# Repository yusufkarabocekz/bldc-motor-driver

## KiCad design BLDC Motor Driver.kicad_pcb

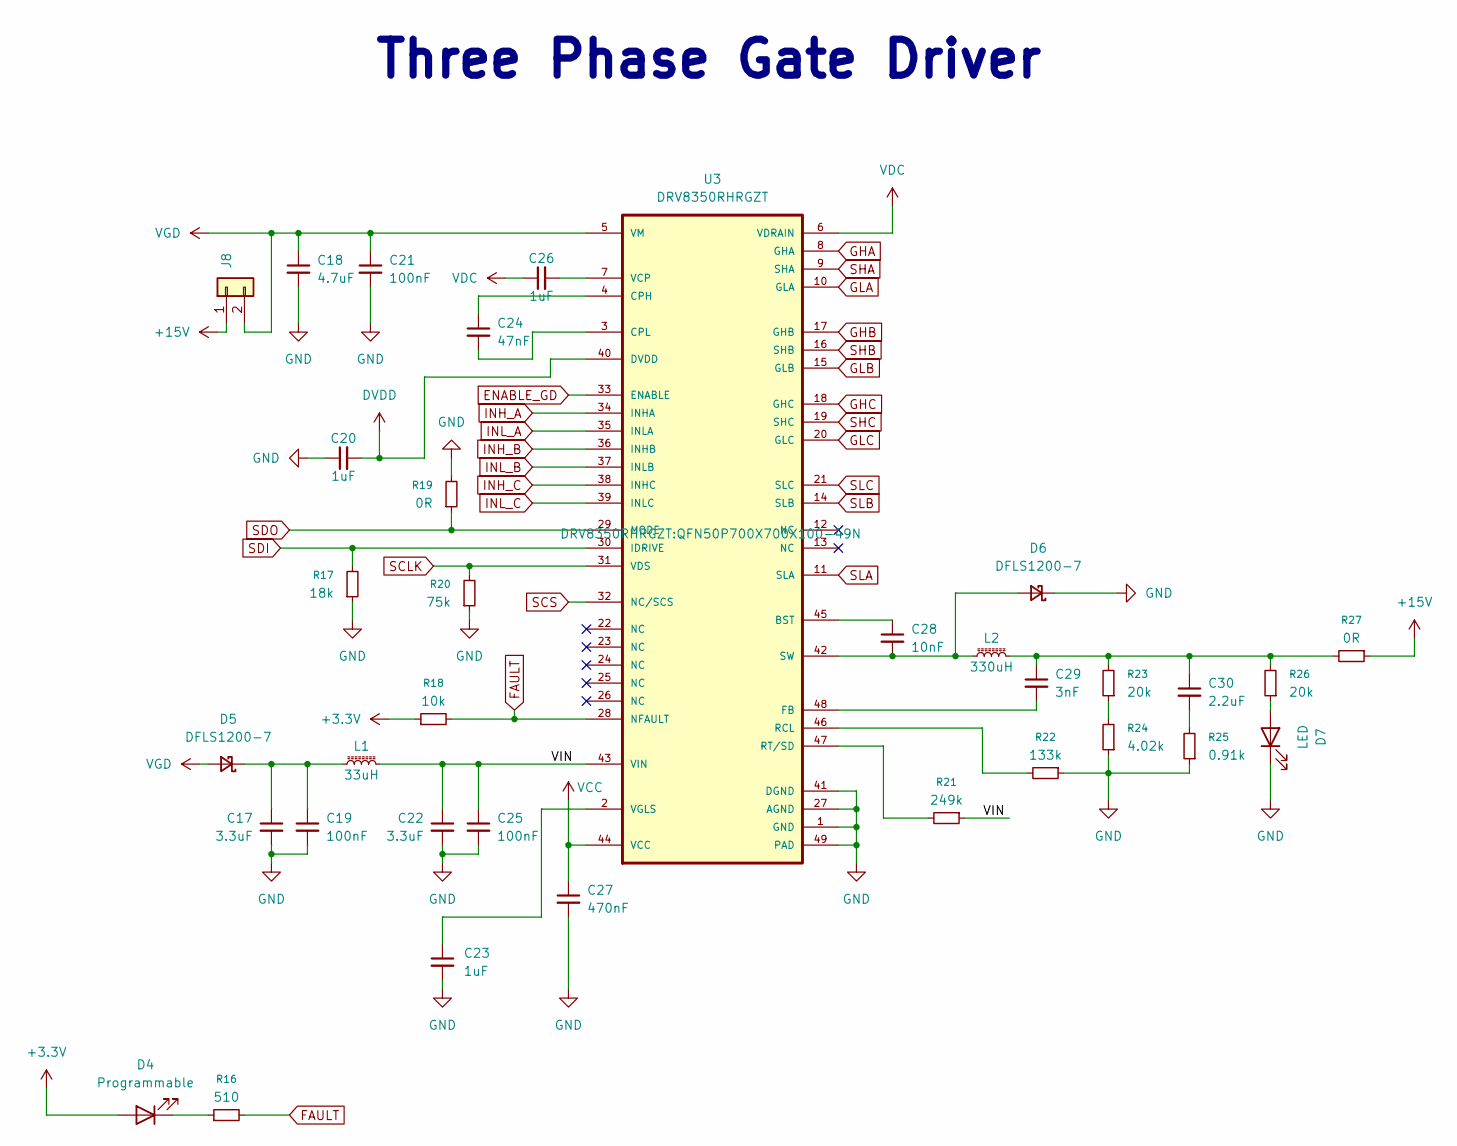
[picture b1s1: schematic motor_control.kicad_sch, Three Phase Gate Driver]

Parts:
C17, C22: 3.3uF; C_1206_3216Metric
C18: 4.7uF; C_2220_5750Metric
C19, C21: 100nF; C_0603_1608Metric
C20, C23, C26: 1uF; C_0402_1005Metric
C24: 47nF; C_0805_2012Metric
C25: 100nF; C_0402_1005Metric
C27: 470nF; C_0402_1005Metric
C28: 10nF; C_0603_1608Metric
C29: 3nF; C_0603_1608Metric
C30: 2.2uF; C_0805_2012Metric
D4: Programmable; LED_0603_1608Metric
D5, D6: DFLS1200-7; Nexperia_CFP3_SOD-123W
D7: LED; LED_0603_1608Metric
J8: Conn_01x02; PinHeader_1x02_P2.54mm_Vertical
L1: 33uH; L_APV_ANR252010
L2: 330uH; L_APV_ANR6028
R16: 510; R_0402_1005Metric
R17: 18k; R_0402_1005Metric
R18: 10k; R_0402_1005Metric
R19, R27: 0R; R_0402_1005Metric
R20: 75k; R_0402_1005Metric
R21: 249k; R_0402_1005Metric
R22: 133k; R_0402_1005Metric
R23, R26: 20k; R_0402_1005Metric
R24: 4.02k; R_0402_1005Metric
R25: 0.91k; R_0402_1005Metric
U3: DRV8350RHRGZT; QFN50P700X700X100-49N

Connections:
+3.3V: D4.2 (A), R18.1; also elsewhere on the board
+15V: J8.1, R27.1; also elsewhere on the board
/3-Phase Motor Control/VIN: C22.1, C25.1, L1.2, R21.1, U3.43 (VIN)
DVDD: C20.2, U3.40 (DVDD)
ENABLE_GD: U3.33 (ENABLE); also elsewhere on the board
FAULT: R16.2, R18.2, U3.28 (NFAULT); also elsewhere on the board
GHA: U3.8 (GHA); also elsewhere on the board
GHB: U3.17 (GHB); also elsewhere on the board
GHC: U3.18 (GHC); also elsewhere on the board
GLA: U3.10 (GLA); also elsewhere on the board
GLB: U3.15 (GLB); also elsewhere on the board
GLC: U3.20 (GLC); also elsewhere on the board
INH_A: U3.34 (INHA); also elsewhere on the board
INH_B: U3.36 (INHB); also elsewhere on the board
INH_C: U3.38 (INHC); also elsewhere on the board
INL_A: U3.35 (INLA); also elsewhere on the board
INL_B: U3.37 (INLB); also elsewhere on the board
INL_C: U3.39 (INLC); also elsewhere on the board
unnamed: C29.1, C30.1, L2.2, R23.2, R26.2, R27.2
unnamed: C30.2, R25.2
unnamed: D4.1 (K), R16.1
unnamed: C17.1, C19.1, D5.1 (K), L1.1
unnamed: C28.2, D6.2 (A), L2.1, U3.42 (SW)
unnamed: D7.2 (A), R26.1
unnamed: R23.1, R24.2
unnamed: C28.1, U3.45 (BST)
unnamed: C24.1, U3.4 (CPH)
unnamed: C24.2, U3.3 (CPL)
unnamed: C29.2, U3.48 (FB)
unnamed: R22.2, U3.46 (RCL)
unnamed: R21.2, U3.47 (RT/SD)
unnamed: C26.2, U3.7 (VCP)
unnamed: C23.1, U3.2 (VGLS)
SCLK: R20.2, U3.31 (VDS); also elsewhere on the board
SCS: U3.32 (NC/SCS); also elsewhere on the board
SDI: R17.2, U3.30 (IDRIVE); also elsewhere on the board
SDO: R19.1, U3.29 (MODE); also elsewhere on the board
SHA: U3.9 (SHA); also elsewhere on the board
SHB: U3.16 (SHB); also elsewhere on the board
SHC: U3.19 (SHC); also elsewhere on the board
SLA: U3.11 (SLA), U3.14 (SLB), U3.21 (SLC); also elsewhere on the board
VCC: C27.1, U3.44 (VCC)
VDC: C26.1, U3.6 (VDRAIN); also elsewhere on the board
VGD: C18.1, C21.1, D5.2 (A), J8.2, U3.5 (VM); also elsewhere on the board

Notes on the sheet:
Three Phase Gate Driver

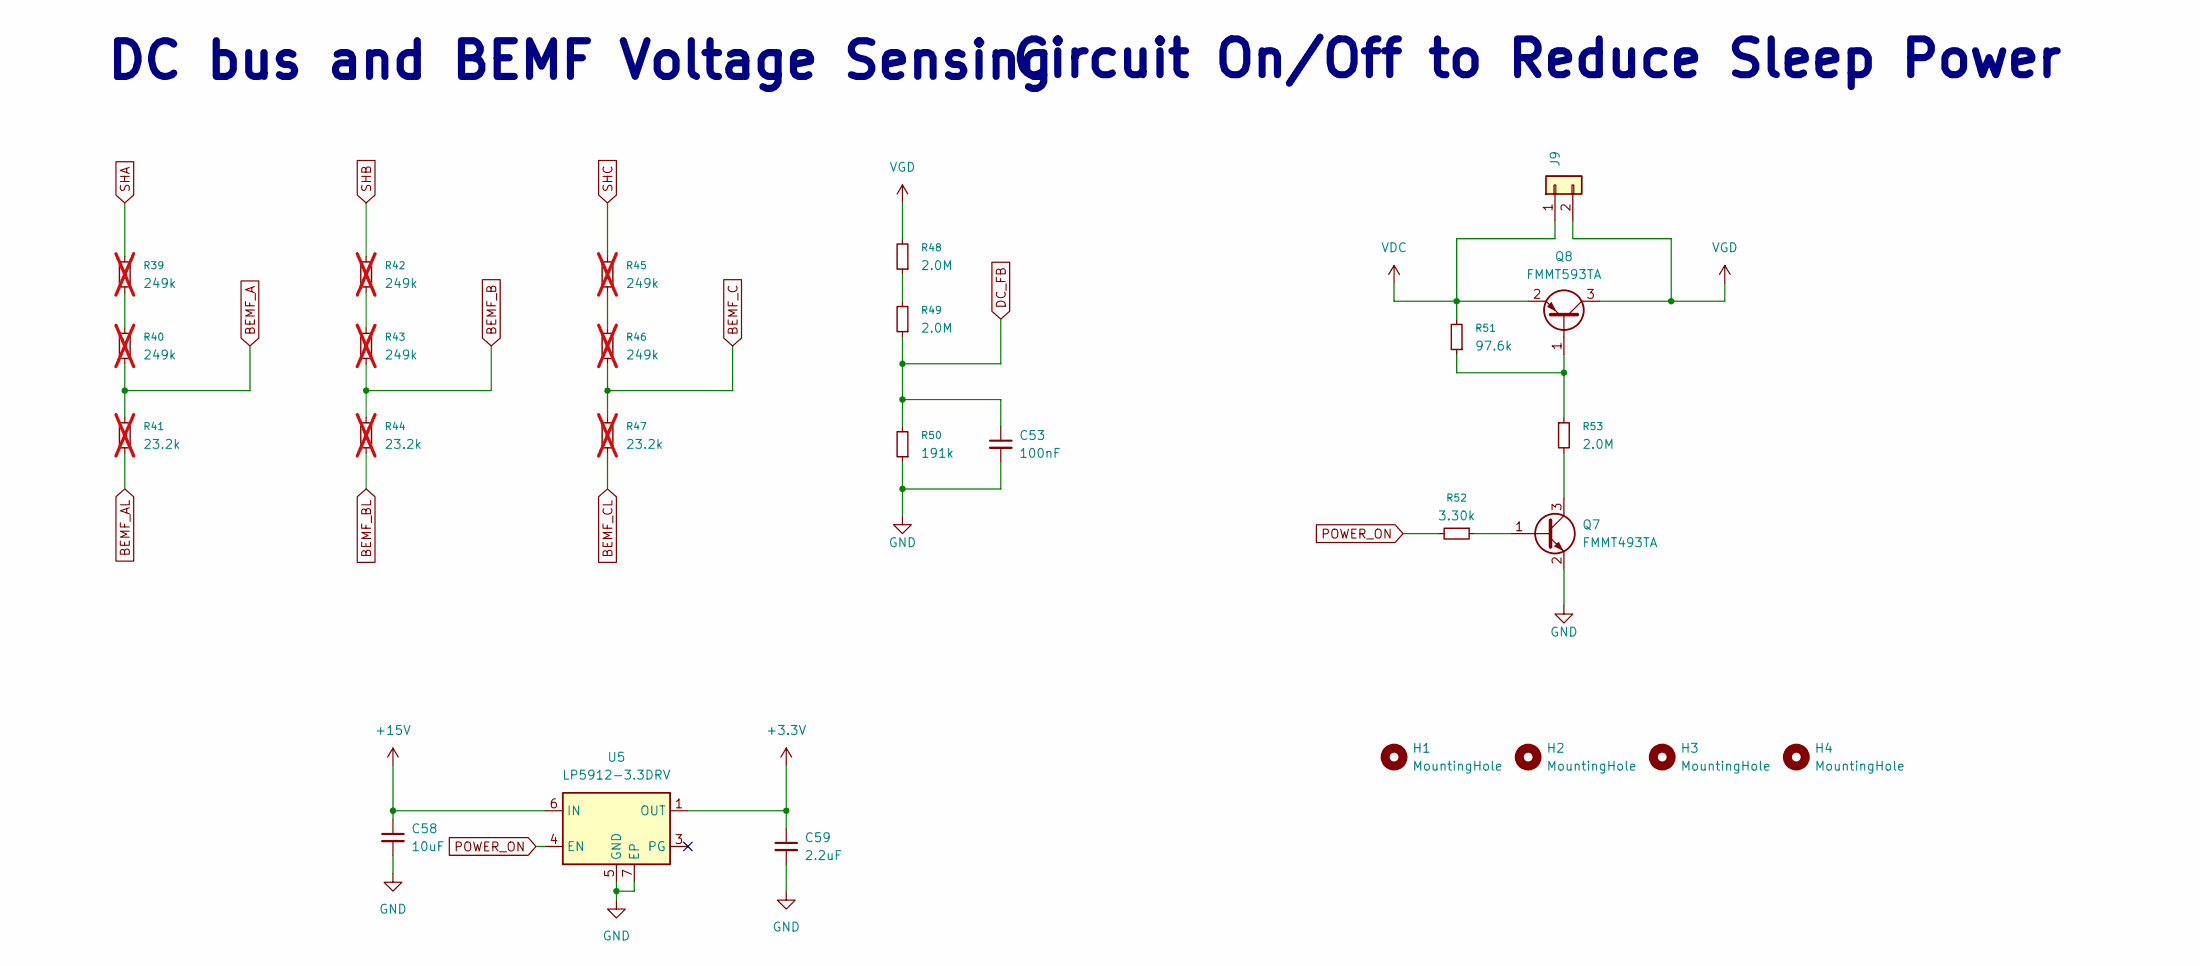
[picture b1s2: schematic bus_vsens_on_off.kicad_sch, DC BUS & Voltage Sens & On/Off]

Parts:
C53: 100nF; C_0402_1005Metric
C58: 10uF; C_1206_3216Metric
C59: 2.2uF; C_0402_1005Metric
H1, H2, H3, H4: MountingHole; MountingHole_3.2mm_M3_ISO14580
J9: Conn_01x02; PinHeader_1x02_P2.54mm_Vertical
Q7: FMMT493TA; SOT-23
Q8: FMMT593TA; SOT-23
R39, R40, R42, R43, R45, R46: 249k; R_0402_1005Metric; not fitted
R41, R44, R47: 23.2k; R_0402_1005Metric; not fitted
R48, R49, R53: 2.0M; R_0402_1005Metric
R50: 191k; R_0402_1005Metric
R51: 97.6k; R_0402_1005Metric
R52: 3.30k; R_0402_1005Metric
U5: LP5912-3.3DRV; WSON-6-1EP_2x2mm_P0.65mm_EP1x1.6mm_ThermalVias

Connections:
+3.3V: C59.1, U5.1 (OUT); also elsewhere on the board
+15V: C58.1, U5.6 (IN); also elsewhere on the board
BEMF_A: R40.1, R41.2; also elsewhere on the board
BEMF_AL: R41.1
BEMF_B: R43.1, R44.2; also elsewhere on the board
BEMF_BL: R44.1
BEMF_C: R46.1, R47.2; also elsewhere on the board
BEMF_CL: R47.1
DC_FB: C53.1, R49.1, R50.2; also elsewhere on the board
unnamed: Q7.1 (B), R52.1
unnamed: Q7.3 (C), R53.2
unnamed: Q8.1 (B), R51.1, R53.1
unnamed: R39.1, R40.2
unnamed: R42.1, R43.2
unnamed: R45.1, R46.2
unnamed: R48.1, R49.2
POWER_ON: R52.2, U5.4 (EN); also elsewhere on the board
SHA: R39.2; also elsewhere on the board
SHB: R42.2; also elsewhere on the board
SHC: R45.2; also elsewhere on the board
VDC: J9.1, Q8.2 (E), R51.2; also elsewhere on the board
VGD: J9.2, Q8.3 (C), R48.2; also elsewhere on the board

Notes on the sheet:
DC bus and BEMF Voltage Sensing
Circuit On/Off to Reduce Sleep Power

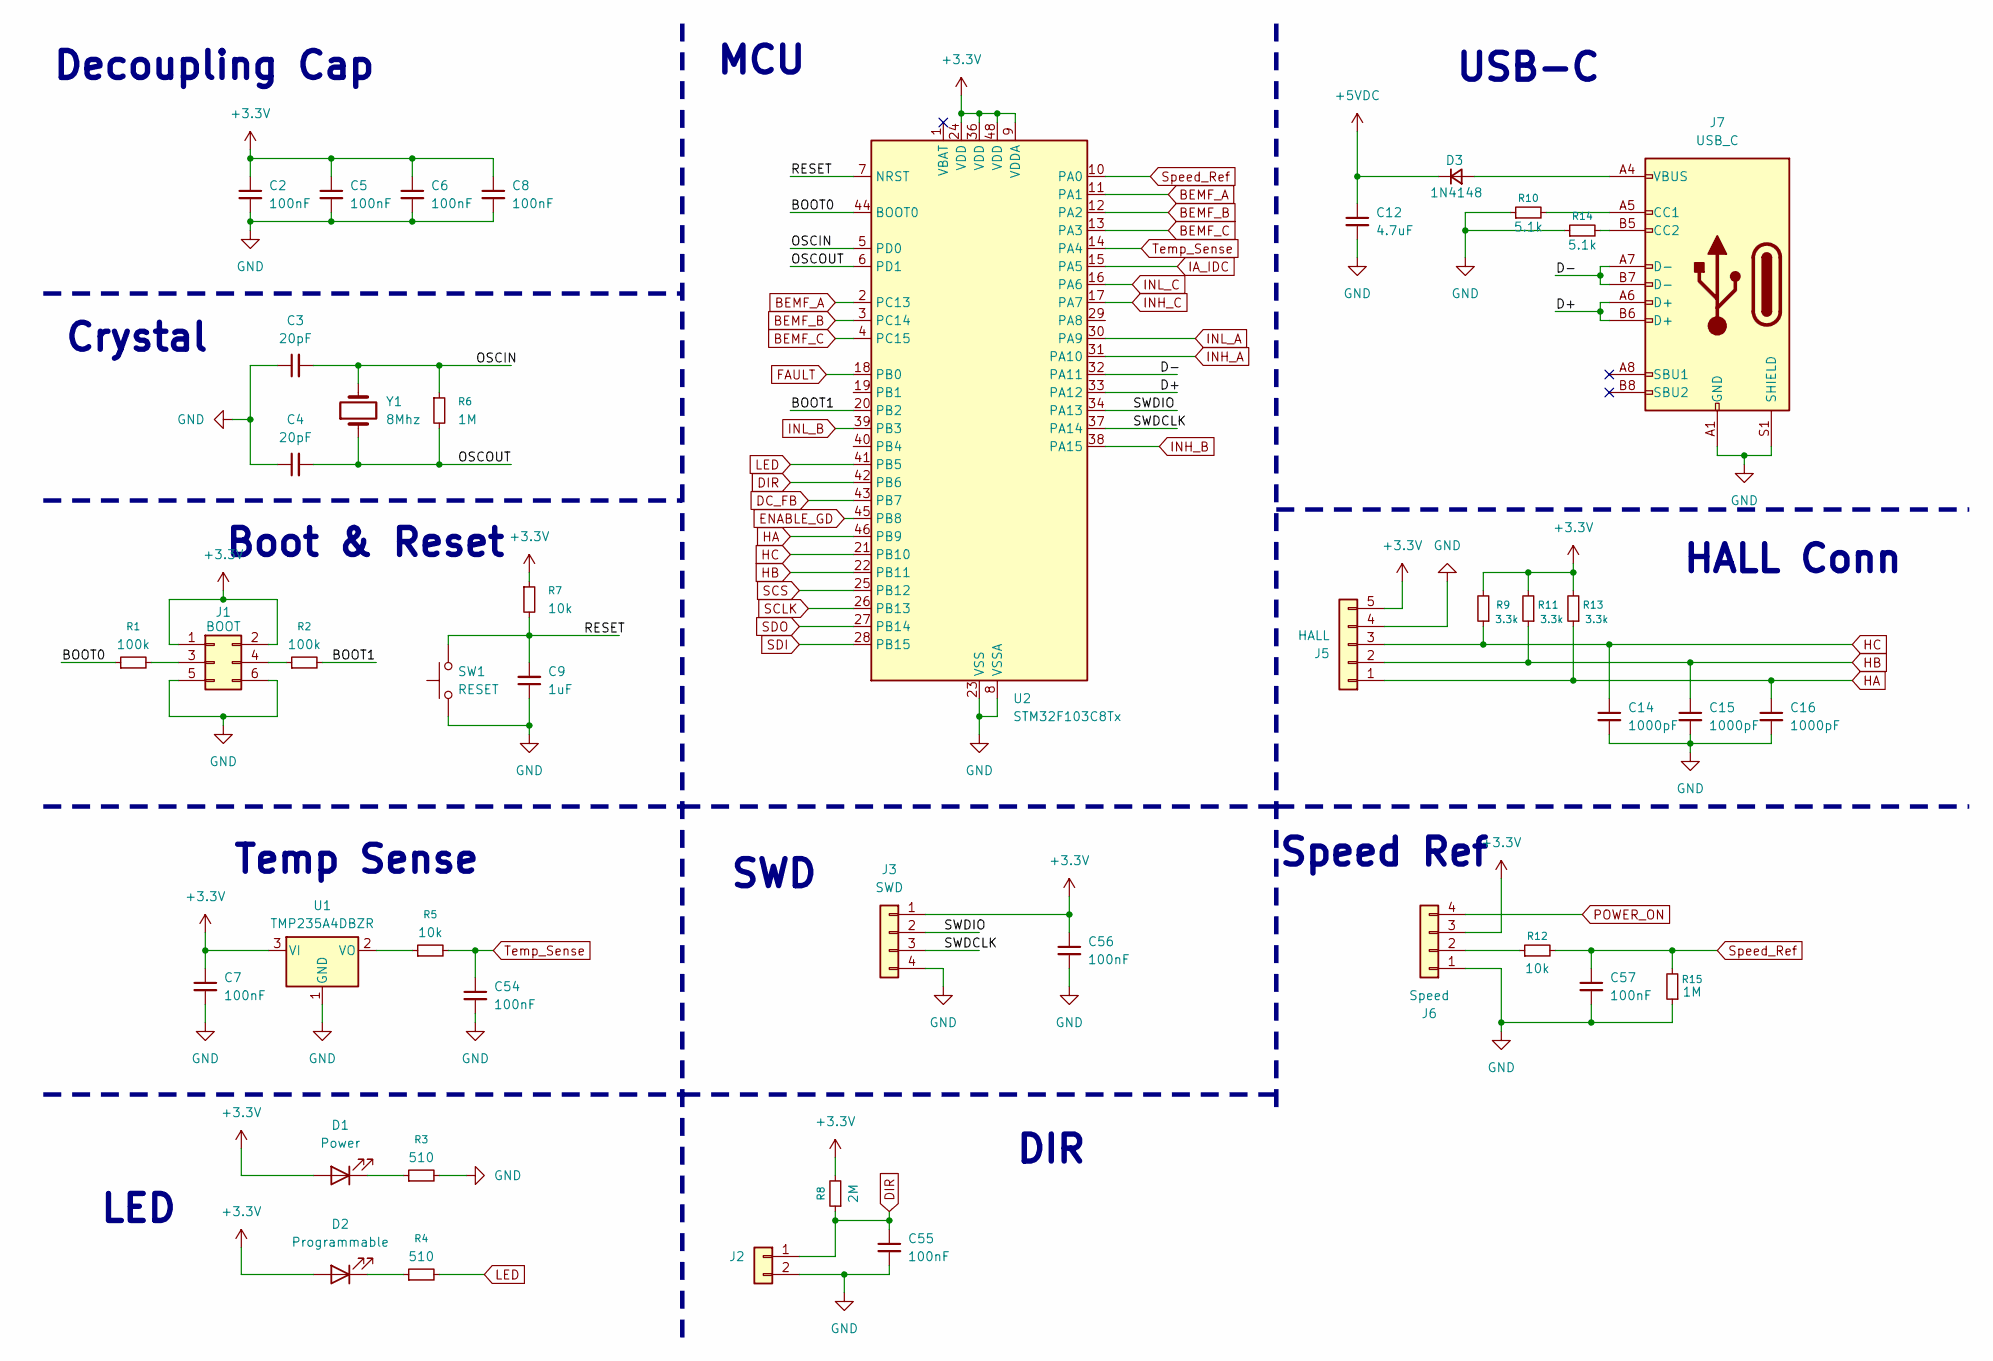
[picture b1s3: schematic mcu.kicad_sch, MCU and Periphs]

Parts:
C2, C5, C6, C7, C8, C54, C55, C56, C57: 100nF; C_0402_1005Metric
C3, C4: 20pF; C_0402_1005Metric
C9: 1uF; C_0402_1005Metric
C12: 4.7uF; C_0805_2012Metric
C14, C15, C16: 1000pF; C_0402_1005Metric
D1: Power; LED_0603_1608Metric
D2: Programmable; LED_0603_1608Metric
D3: 1N4148; D_SMA
J1: BOOT; PinHeader_2x03_P2.54mm_Vertical
J2: Conn_01x02; PinHeader_1x02_P2.54mm_Vertical
J3: SWD; PinHeader_1x04_P2.54mm_Vertical
J5: HALL; PinSocket_1x05_P2.54mm_Vertical
J6: Speed; PinHeader_1x04_P2.54mm_Vertical
J7: USB_C; USB_C_Receptacle_GCT_USB4105-xx-A_16P_TopMnt_Horizontal
R1, R2: 100k; R_0402_1005Metric
R3, R4: 510; R_0402_1005Metric
R5, R7, R12: 10k; R_0402_1005Metric
R6, R15: 1M; R_0402_1005Metric
R8: 2M; R_0402_1005Metric
R9, R11, R13: 3.3k; R_0402_1005Metric
R10, R14: 5.1k; R_0402_1005Metric
SW1: RESET; SW_PUSH_1P1T_6x3.5mm_H5.0_APEM_MJTP1250
U1: TMP235A4DBZR; SOT-23
U2: STM32F103C8Tx; LQFP-48_7x7mm_P0.5mm
Y1: 8Mhz; Crystal_HC18-U_Vertical

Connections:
+3.3V: C2.1, C5.1, C6.1, C7.1, C8.1, C56.1, D1.2 (A), D2.2 (A), J1.1, J1.2, J3.1, J5.5, J6.3, R7.1, R8.2, R9.2, R11.2, R13.2, U1.3 (VI), U2.9 (VDDA), U2.24 (VDD), U2.36 (VDD), U2.48 (VDD); also elsewhere on the board
+5VDC: C12.1, D3.1 (K)
/STM32F103 MCU/BOOT0: R1.1, U2.44 (BOOT0)
/STM32F103 MCU/BOOT1: R2.2, U2.20 (PB2)
/STM32F103 MCU/D+: J7.A6 (D+), J7.B6 (D+), U2.33 (PA12)
/STM32F103 MCU/D-: J7.A7 (D-), J7.B7 (D-), U2.32 (PA11)
/STM32F103 MCU/OSCIN: C3.2, R6.1, U2.5 (PD0), Y1.2
/STM32F103 MCU/OSCOUT: C4.2, R6.2, U2.6 (PD1), Y1.1
/STM32F103 MCU/SWDCLK: J3.3, U2.37 (PA14)
/STM32F103 MCU/SWDIO: J3.2, U2.34 (PA13)
BEMF_A: U2.2 (PC13), U2.11 (PA1); also elsewhere on the board
BEMF_B: U2.3 (PC14), U2.12 (PA2); also elsewhere on the board
BEMF_C: U2.4 (PC15), U2.13 (PA3); also elsewhere on the board
DC_FB: U2.43 (PB7); also elsewhere on the board
DIR: C55.1, J2.1, R8.1, U2.42 (PB6)
ENABLE_GD: U2.45 (PB8); also elsewhere on the board
FAULT: U2.18 (PB0); also elsewhere on the board
HA: C16.1, J5.1, R13.1, U2.46 (PB9)
HB: C15.1, J5.2, R11.1, U2.22 (PB11)
HC: C14.1, J5.3, R9.1, U2.21 (PB10)
IA_IDC: U2.15 (PA5); also elsewhere on the board
INH_A: U2.31 (PA10); also elsewhere on the board
INH_B: U2.38 (PA15); also elsewhere on the board
INH_C: U2.17 (PA7); also elsewhere on the board
INL_A: U2.30 (PA9); also elsewhere on the board
INL_B: U2.39 (PB3); also elsewhere on the board
INL_C: U2.16 (PA6); also elsewhere on the board
LED: R4.2, U2.41 (PB5)
unnamed: D1.1 (K), R3.1
unnamed: D2.1 (K), R4.1
unnamed: D3.2 (A), J7.A4 (VBUS), J7.A9 (VBUS), J7.B4 (VBUS), J7.B9 (VBUS)
unnamed: J1.3, R1.2
unnamed: J1.4, R2.1
unnamed: J6.2, R12.1
unnamed: J7.A5 (CC1), R10.2
unnamed: J7.B5 (CC2), R14.2
unnamed: R5.1, U1.2 (VO)
POWER_ON: J6.4; also elsewhere on the board
SCLK: U2.26 (PB13); also elsewhere on the board
SCS: U2.25 (PB12); also elsewhere on the board
SDI: U2.28 (PB15); also elsewhere on the board
SDO: U2.27 (PB14); also elsewhere on the board
Speed_Ref: C57.1, R12.2, R15.2, U2.10 (PA0)
Temp_Sense: C54.1, R5.2, U2.14 (PA4)

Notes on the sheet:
MCU
DIR
SWD
Temp Sense
Speed Ref
Crystal
HALL Conn
Boot & Reset
Decoupling Cap
LED
USB-C

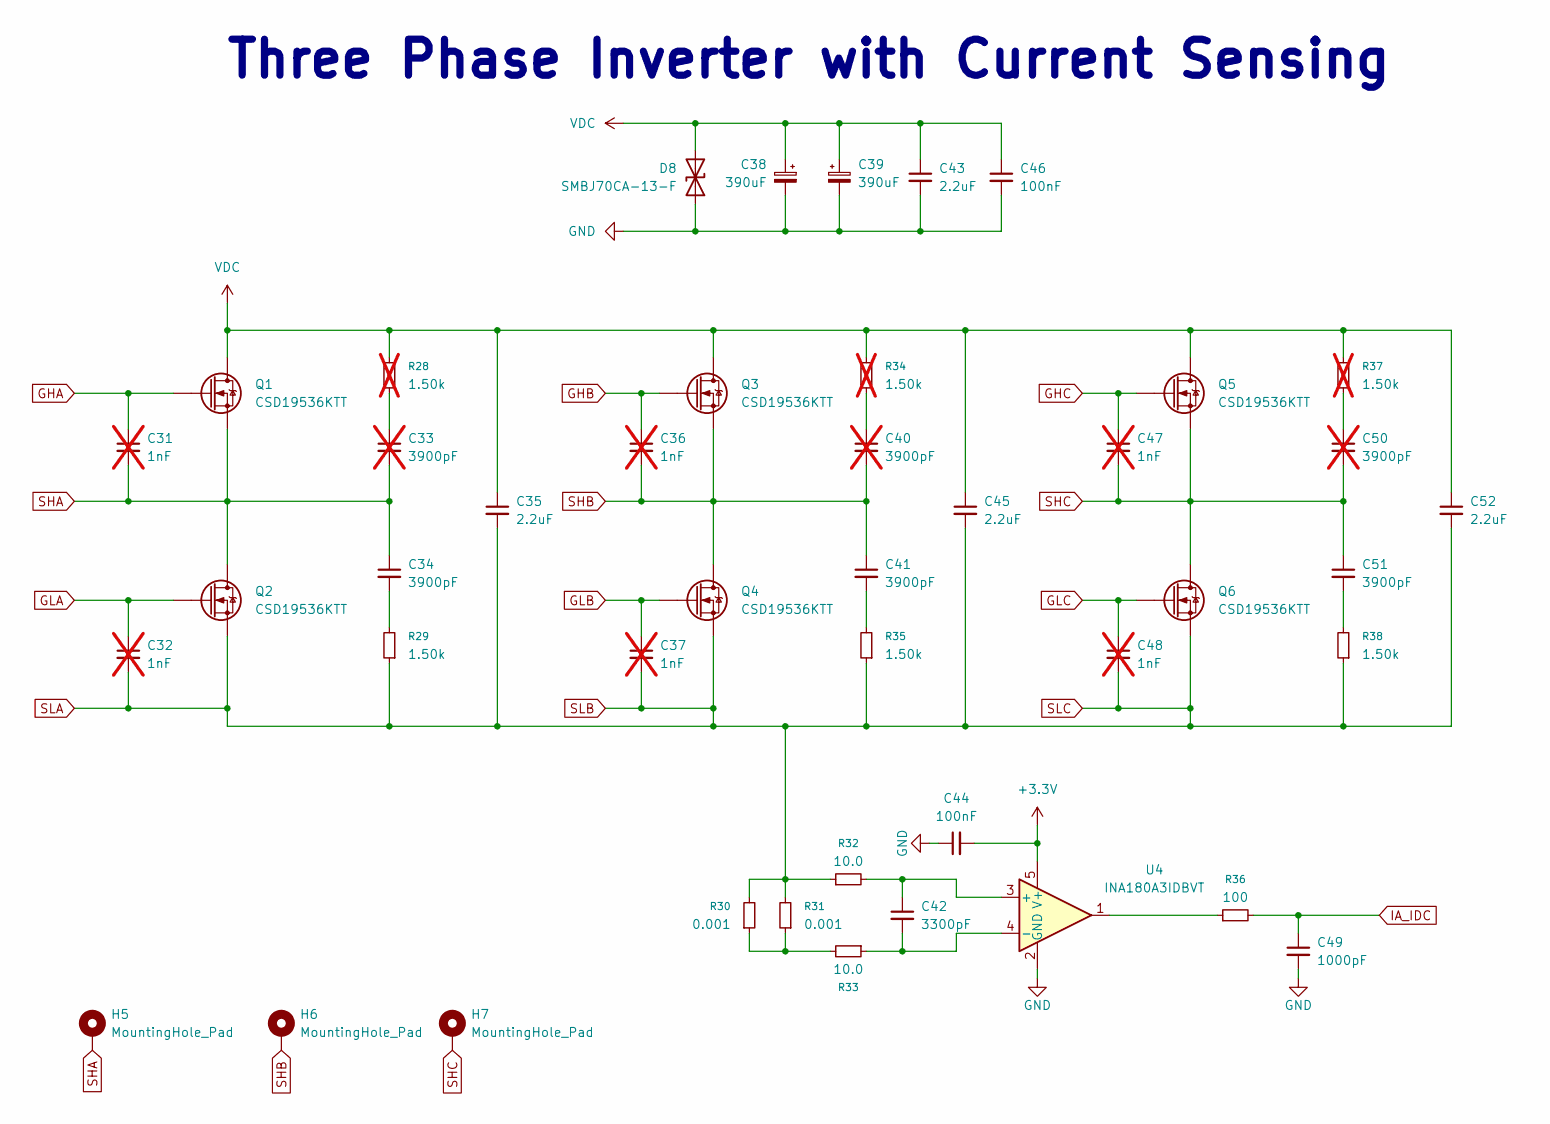
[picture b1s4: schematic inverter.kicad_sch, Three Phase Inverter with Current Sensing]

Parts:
C31, C32, C36, C37, C47, C48: 1nF; C_0603_1608Metric; not fitted
C33, C40, C50: 3900pF; C_1206_3216Metric; not fitted
C34, C41, C51: 3900pF; C_1206_3216Metric
C35, C43, C45, C52: 2.2uF; C_1206_3216Metric
C38, C39: 390uF; CP_Radial_D16.0mm_P7.50mm
C42: 3300pF; C_0402_1005Metric
C44: 100nF; C_0402_1005Metric
C46: 100nF; C_1206_3216Metric
C49: 1000pF; C_0402_1005Metric
D8: SMBJ70CA-13-F; D_SMB
H5, H6, H7: MountingHole_Pad; MountingHole_2.2mm_M2_Pad_Via
Q1, Q2, Q3, Q4, Q5, Q6: CSD19536KTT; TO-263-2
R28, R34, R37: 1.50k; R_1206_3216Metric; not fitted
R29, R35, R38: 1.50k; R_1206_3216Metric
R30, R31: 0.001; R_2512_6332Metric
R32, R33: 10.0; R_0402_1005Metric
R36: 100; R_0402_1005Metric
U4: INA180A3IDBVT; SOT-23-5

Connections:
+3.3V: C44.2, U4.5 (V+); also elsewhere on the board
GHA: C31.1, Q1.1 (G); also elsewhere on the board
GHB: C36.1, Q3.1 (G); also elsewhere on the board
GHC: C47.1, Q5.1 (G); also elsewhere on the board
GLA: C32.1, Q2.1 (G); also elsewhere on the board
GLB: C37.1, Q4.1 (G); also elsewhere on the board
GLC: C48.1, Q6.1 (G); also elsewhere on the board
IA_IDC: C49.1, R36.2; also elsewhere on the board
unnamed: C33.1, R28.1
unnamed: C34.2, R29.2
unnamed: C40.1, R34.1
unnamed: C41.2, R35.2
unnamed: C50.1, R37.1
unnamed: C51.2, R38.2
unnamed: R30.1, R31.1, R33.2
unnamed: R36.1, U4.1
unnamed: C42.1, R32.2, U4.3 (+)
unnamed: C42.2, R33.1, U4.4 (-)
SHA: C31.2, C33.2, C34.1, H5.1, Q1.3 (S), Q2.2 (D); also elsewhere on the board
SHB: C36.2, C40.2, C41.1, H6.1, Q3.3 (S), Q4.2 (D); also elsewhere on the board
SHC: C47.2, C50.2, C51.1, H7.1, Q5.3 (S), Q6.2 (D); also elsewhere on the board
SLA: C32.2, C35.2, C37.2, C45.2, C48.2, C52.2, Q2.3 (S), Q4.3 (S), Q6.3 (S), R29.1, R30.2, R31.2, R32.1, R35.1, R38.1; also elsewhere on the board
VDC: C35.1, C38.1, C39.1, C43.1, C45.1, C46.1, C52.1, D8.2 (A2), Q1.2 (D), Q3.2 (D), Q5.2 (D), R28.2, R34.2, R37.2; also elsewhere on the board

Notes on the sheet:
Three Phase Inverter with Current Sensing

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
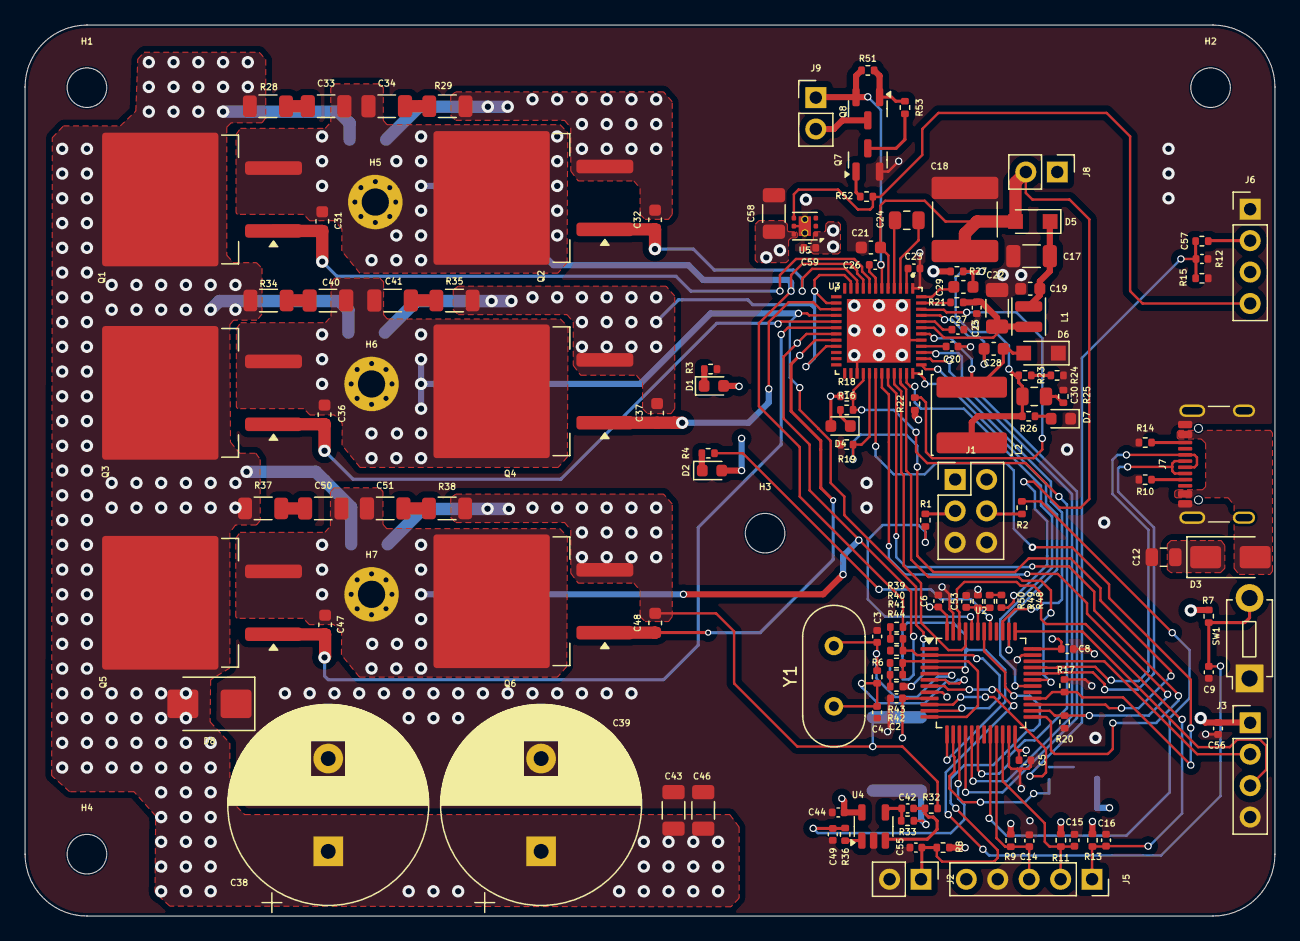
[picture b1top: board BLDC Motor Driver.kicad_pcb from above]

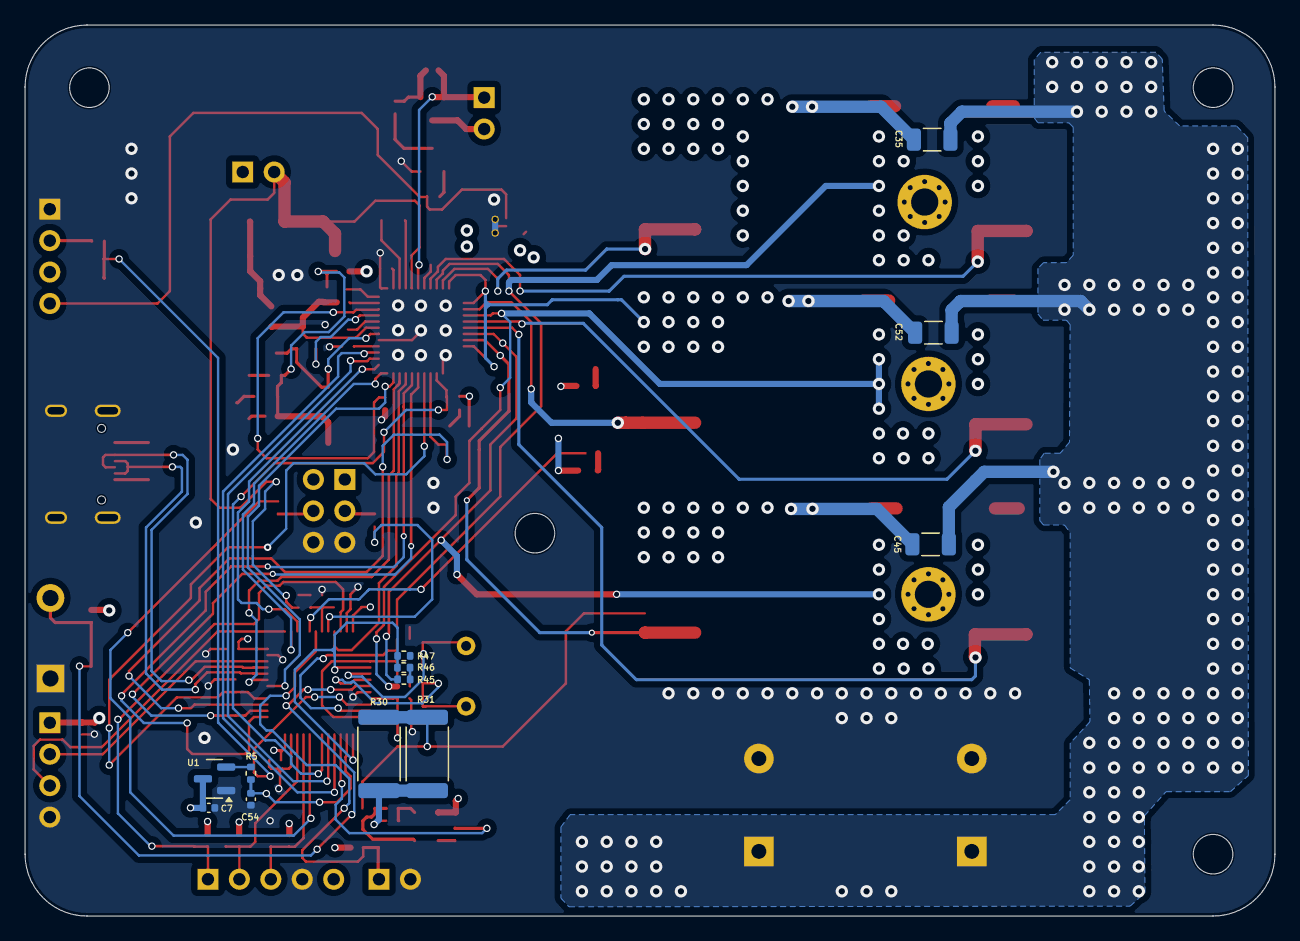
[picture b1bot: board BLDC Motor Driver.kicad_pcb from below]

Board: 4 copper layers, 101.0 x 72.0 mm, 148 parts (12 on the bottom side), 94 nets.

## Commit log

2025-06-10 3 phase gate driver schematic
2025-06-11 schematic finished
2025-06-12 some routing processing
2025-06-13 finished the pcb design
